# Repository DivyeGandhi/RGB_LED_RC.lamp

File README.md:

# RGB_LED_RC.lamp
I am very Excited to show you all that for the mini project of Electronics Design Workshop, I Created a Remote controlled RGB Lamp with tunable RGB and brightness to make 16,777,216 colours. It also has an Auto adjust to room Brightness button to adjust the brightness which best suits the room.

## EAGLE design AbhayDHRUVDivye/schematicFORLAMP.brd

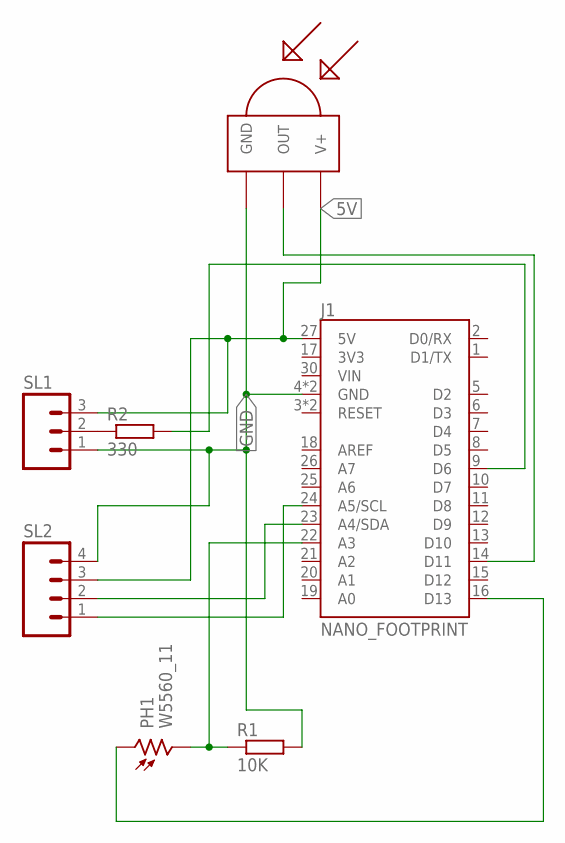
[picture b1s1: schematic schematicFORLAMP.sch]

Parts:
J1: NANO_FOOTPRINT; NANO
PH1: W5560_11; W55XX
R1: 10K; 0207/10
R2: 330; 0207/10
SL1: M03; 03P
SL2: M04; 04P
U$1: TSOP1838; TSOP18XX

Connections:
5V: J1.27 (5V), SL1.3, SL2.3, U$1.VCC (V+)
GND: J1.4 (GND), J1.29 (GND), R1.2, SL1.1, SL2.4, U$1.GND
unnamed: R2.1, SL1.2
unnamed: J1.9 (D6), R2.2
unnamed: J1.22 (A3), PH1.2, R1.1
unnamed: J1.14 (D11), U$1.OUT
unnamed: J1.16 (D13), PH1.1
unnamed: J1.23 (A4/SDA), SL2.2
unnamed: J1.24 (A5/SCL), SL2.1

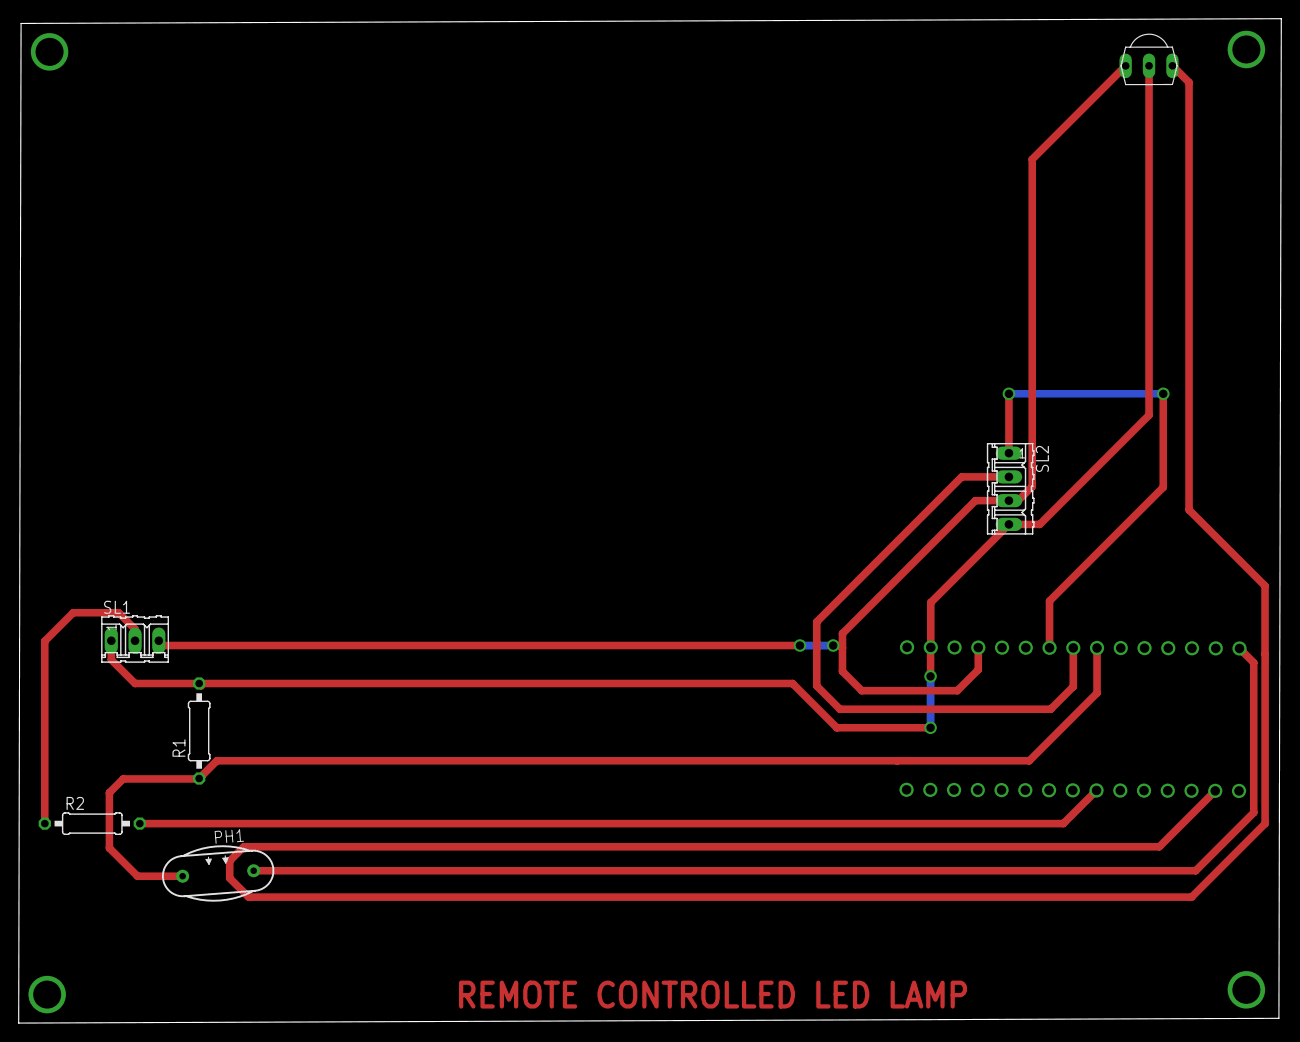
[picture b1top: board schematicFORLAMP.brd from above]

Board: 2 copper layers, 135.1 x 107.4 mm, 7 parts (0 on the bottom side), 9 nets.

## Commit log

2023-07-18 Create added sketch.ino
    RGB Lamp with tunable RGB and brightness to make 16,777,216 colors, Auto adjust to room Brightness button to adjust the brightness which best suits the room , interesting patterns, the lamp can save 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
2023-07-18 Added Board Files
2023-07-18 Add files via upload
    added Documentation

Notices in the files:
parts and their libraries:
SparkFun-Boards: Licensing: Creative Commons ShareAlike 4.0 International - https://creativecommons.org/licenses/by-sa/4.0
